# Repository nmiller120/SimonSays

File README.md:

# Simon Says

Project was undertaken to learn the process of PCB design and prototyping. PCB was designed using KiCad, source code written in the Arduino IDE.

Link To Game Being Played: https://www.youtube.com/watch?v=HIm8sEf_zMo

# Close-up of Board

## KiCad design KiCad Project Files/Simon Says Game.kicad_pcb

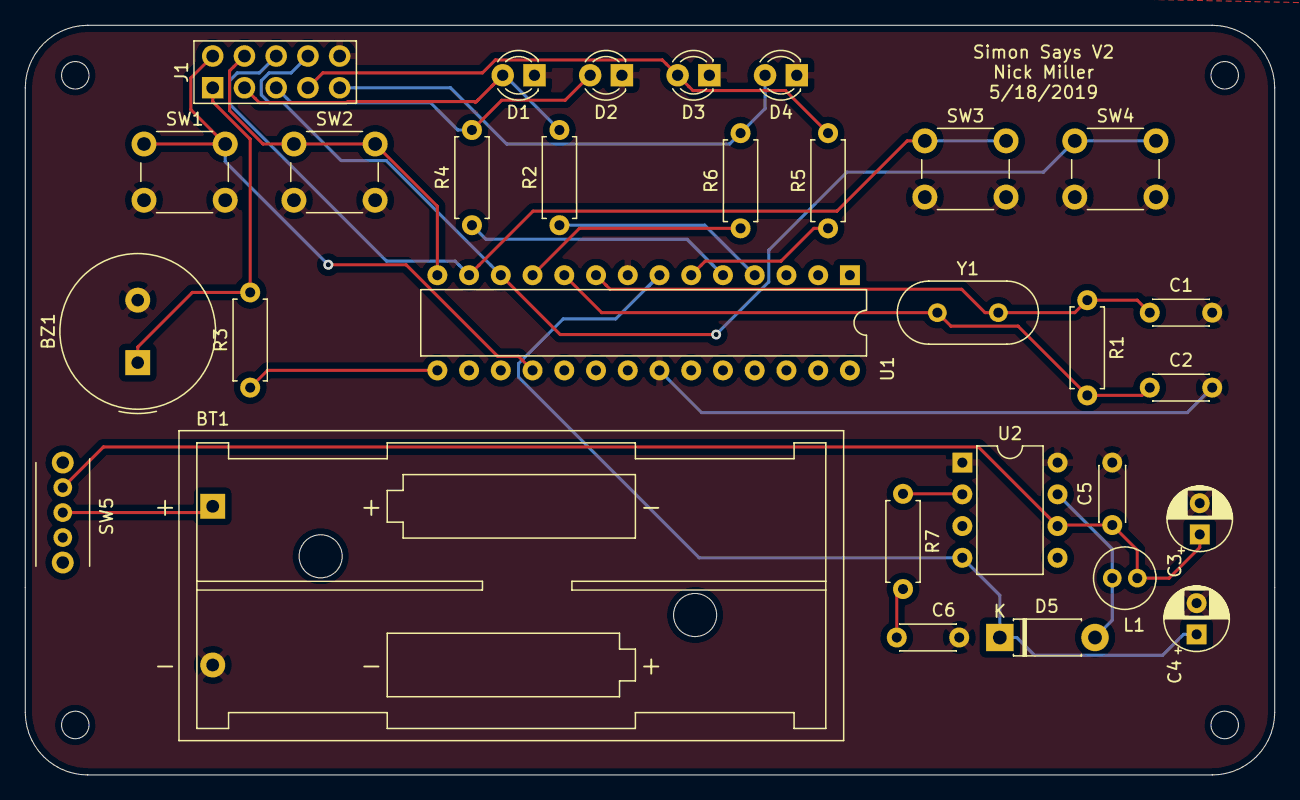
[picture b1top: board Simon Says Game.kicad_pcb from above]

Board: 2 copper layers, 100.0 x 60.0 mm, 30 parts (0 on the bottom side), 23 nets.

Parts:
BT1: Battery; BatteryHolder_Keystone_2468_2xAAA
BZ1: Buzzer; Buzzer_TDK_PS1240P02BT_D12.2mm_H6.5mm
C1, C2: 22pF; C_Disc_D4.3mm_W1.9mm_P5.00mm
C3, C4: 100 uF; CP_Radial_D5.0mm_P2.50mm
C5: 0.1 uF; C_Disc_D4.3mm_W1.9mm_P5.00mm
C6: 0.01 uF; C_Disc_D4.3mm_W1.9mm_P5.00mm
D1, D2, D3, D4: LED; LED_D3.0mm
D5: 1N5819-T; D_DO-41_SOD81_P7.62mm_Horizontal
J1: Conn_01x10; IDC-Header_2x05_P2.54mm_Vertical
L1: 10 uH; Inductor_10uH
R1: 1M; R_Axial_DIN0207_L6.3mm_D2.5mm_P7.62mm_Horizontal
R2, R4, R5, R6: 200; R_Axial_DIN0207_L6.3mm_D2.5mm_P7.62mm_Horizontal
R3: 100; R_Axial_DIN0207_L6.3mm_D2.5mm_P7.62mm_Horizontal
R7: 20k; R_Axial_DIN0207_L6.3mm_D2.5mm_P7.62mm_Horizontal
SW1, SW2, SW3, SW4: SW_Push; SW_PUSH_6mm
SW5: SW_SPDT; 1825232-1
U1: ATmega328P-PU; DIP-28_W7.62mm
U2: LT1302CN8-5PBF; DIP-8_W7.62mm
Y1: 16Mhz; Crystal_HC49-U_Vertical

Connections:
+5V: C4.1, D5.1, U1.7, U2.4
GND: BT1.2, BZ1.2, C1.2, C2.2, C3.2, C4.2, C5.2, C6.2, D1.1, D2.1, D3.1, D4.1, J1.10, SW1.2, SW2.2, SW3.2, SW4.2, U1.8, U1.22, U2.1, U2.8
unnamed: BT1.1, SW5.2
unnamed: BZ1.1, J1.1, R3.2
unnamed: C1.1, R1.1, U1.9, Y1.2
unnamed: C2.1, R1.2, U1.10, Y1.1
unnamed: C3.1, C5.1, L1.2, SW5.3, U2.6
unnamed: C6.1, R7.2
unnamed: D1.2, J1.3, R2.2
unnamed: D2.2, J1.5, R4.2
unnamed: D3.2, J1.7, R5.2
unnamed: D4.2, J1.9, R6.2
unnamed: D5.2, L1.1, U2.7
unnamed: J1.2, SW1.1, U1.18
unnamed: J1.4, SW2.1, U1.14
unnamed: J1.6, SW3.1, U1.13
unnamed: J1.8, SW4.1, U1.12
unnamed: R2.1, U1.4
unnamed: R3.1, U1.15
unnamed: R4.1, U1.5
unnamed: R5.1, U1.6
unnamed: R6.1, U1.11
unnamed: R7.1, U2.2

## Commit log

2019-09-19 finalizing code comments
2019-09-20 Update SimonGame_Code.ino
    Improve text wrapping in comments
2025-11-23 Remove dependency on PinChangeInt.h. Lengthened debounce time.
